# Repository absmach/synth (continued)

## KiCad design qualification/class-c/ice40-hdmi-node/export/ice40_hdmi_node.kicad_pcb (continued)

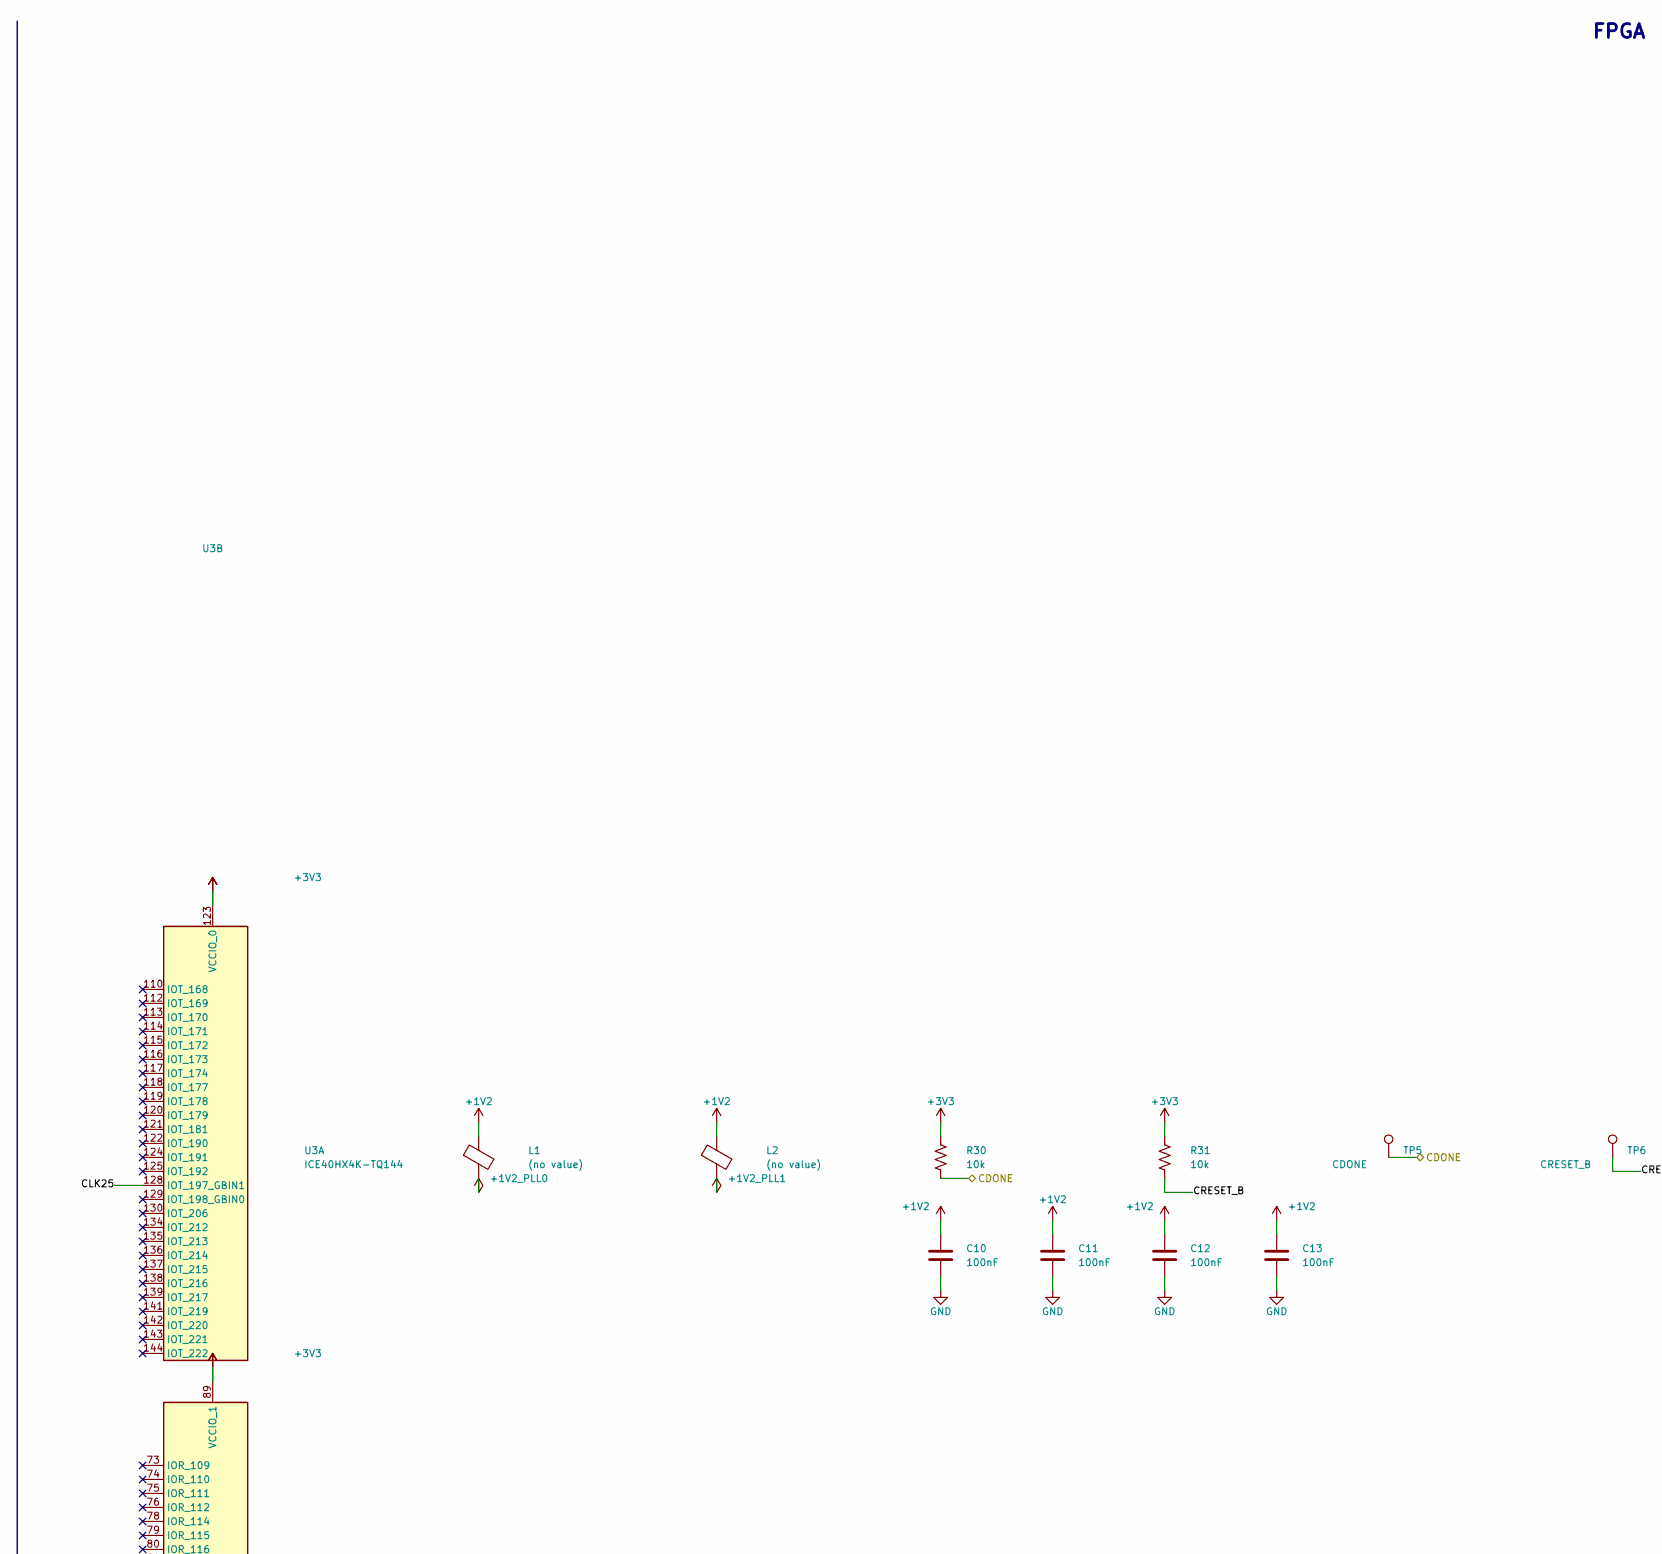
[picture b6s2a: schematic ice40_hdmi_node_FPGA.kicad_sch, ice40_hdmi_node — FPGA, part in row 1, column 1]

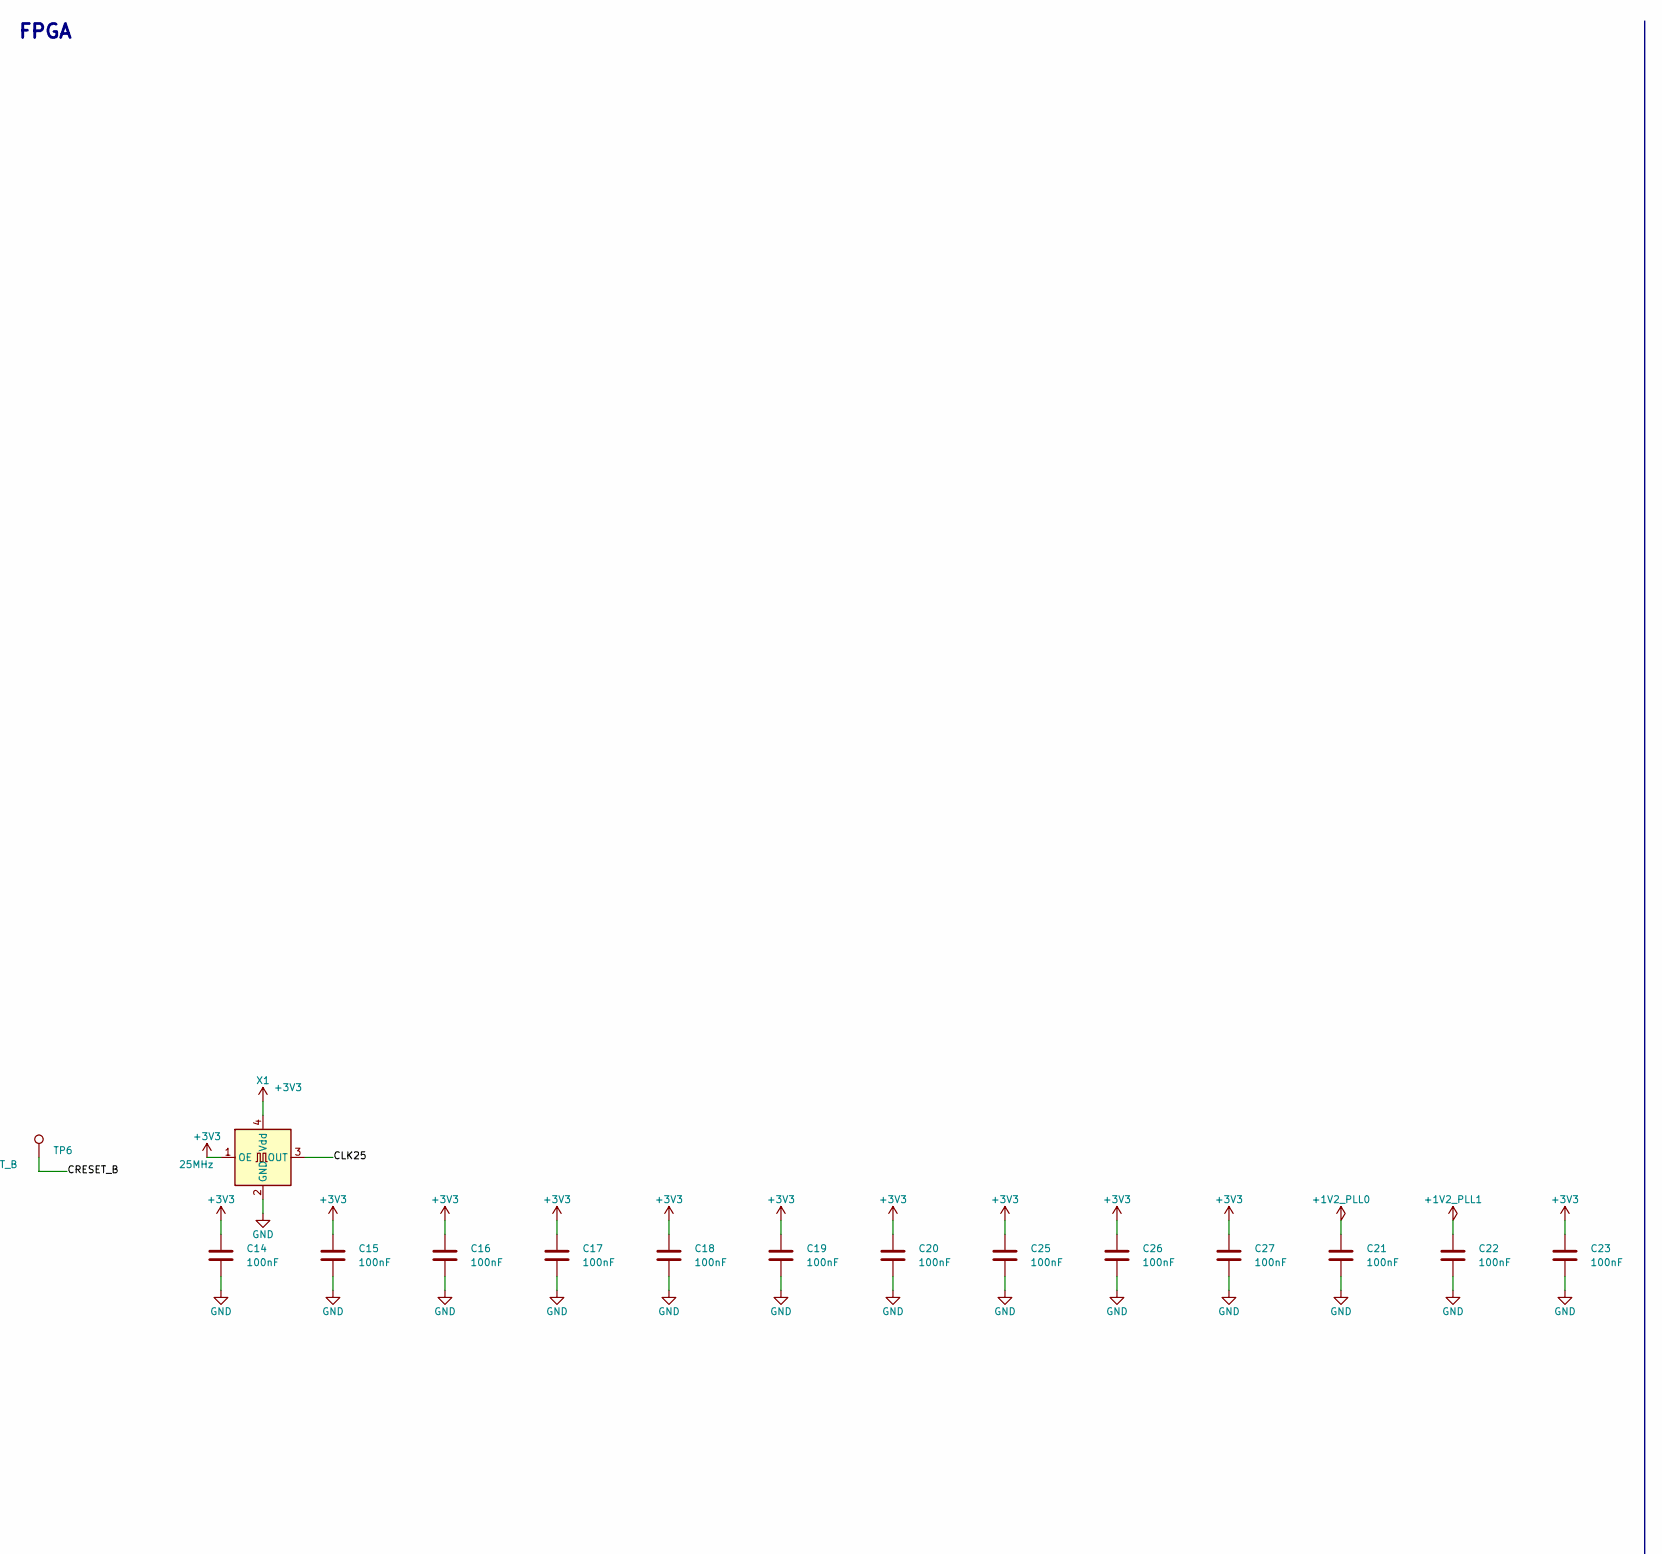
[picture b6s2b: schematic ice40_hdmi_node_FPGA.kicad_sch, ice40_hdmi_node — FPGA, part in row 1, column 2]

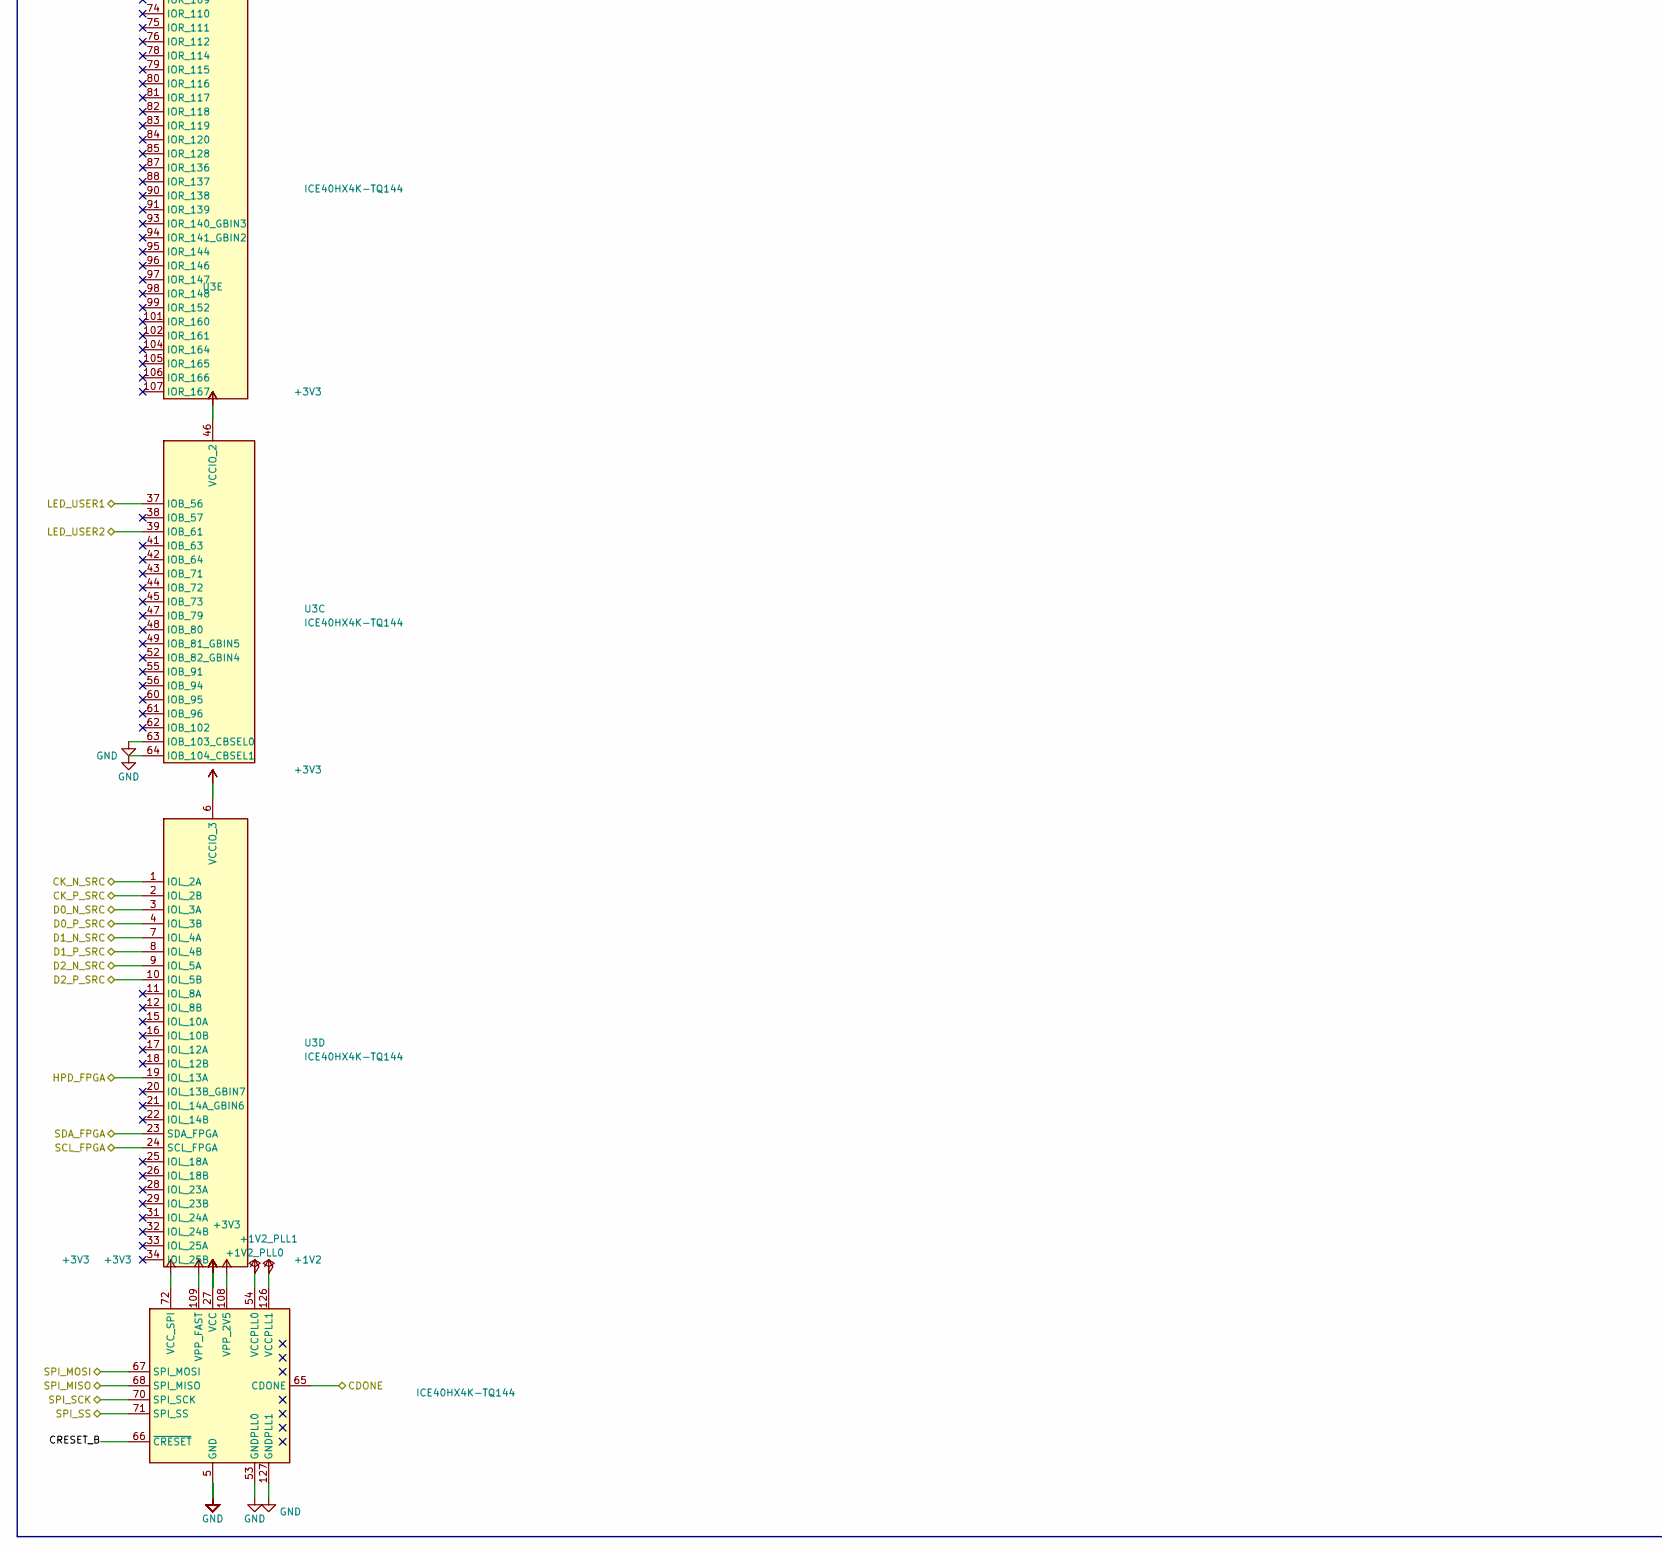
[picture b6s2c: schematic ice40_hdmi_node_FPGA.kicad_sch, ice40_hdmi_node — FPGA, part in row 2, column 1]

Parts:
C10, C11, C12, C13, C14, C15, C16, C17, C18, C19, C20, C21, C22, C23, C25, C26, C27: 100nF; C_0402_1005Metric
L1, L2: (no value); L_0603_1608Metric
R30, R31: 10k; R_0603_1608Metric
TP5: CDONE; TestPoint_Pad_D1.5mm
TP6: CRESET_B; TestPoint_Pad_D1.5mm
U3: ICE40HX4K-TQ144; TQFP-144_20x20mm_P0.5mm; MPN ICE40HX4K-TQ144
X1: 25MHz; Oscillator_SMD_SiT_PQFN-4Pin_5.0x3.2mm

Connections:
+1V2: C10.1, C11.1, C12.1, C13.1, L1.1, L2.1, U3.27 (VCC), U3.40 (VCC), U3.92 (VCC), U3.111 (VCC); also elsewhere on the board
+1V2_PLL0: C21.1, L1.2, U3.54 (VCCPLL0)
+1V2_PLL1: C22.1, L2.2, U3.126 (VCCPLL1)
+3V3: C14.1, C15.1, C16.1, C17.1, C18.1, C19.1, C20.1, C23.1, C25.1, C26.1, C27.1, R30.1, R31.1, U3.6 (VCCIO_3), U3.30 (VCCIO_3), U3.46 (VCCIO_2), U3.57 (VCCIO_2), U3.72 (VCC_SPI), U3.89 (VCCIO_1), U3.100 (VCCIO_1), U3.108 (VPP_2V5), U3.109 (VPP_FAST), U3.123 (VCCIO_0), U3.131 (VCCIO_0), X1.1 (OE), X1.4 (Vdd); also elsewhere on the board
CDONE: R30.2, TP5.1, U3.65 (CDONE); also elsewhere on the board
CK_N_SRC: U3.1 (IOL_2A); also elsewhere on the board
CK_P_SRC: U3.2 (IOL_2B); also elsewhere on the board
CLK25: U3.128 (IOT_197_GBIN1), X1.3 (OUT)
CRESET_B: R31.2, TP6.1, U3.66 (~CRESET)
D0_N_SRC: U3.3 (IOL_3A); also elsewhere on the board
D0_P_SRC: U3.4 (IOL_3B); also elsewhere on the board
D1_N_SRC: U3.7 (IOL_4A); also elsewhere on the board
D1_P_SRC: U3.8 (IOL_4B); also elsewhere on the board
D2_N_SRC: U3.9 (IOL_5A); also elsewhere on the board
D2_P_SRC: U3.10 (IOL_5B); also elsewhere on the board
GND: C10.2, C11.2, C12.2, C13.2, C14.2, C15.2, C16.2, C17.2, C18.2, C19.2, C20.2, C21.2, C22.2, C23.2, C25.2, C26.2, C27.2, U3.5 (GND), U3.13 (GND), U3.14 (GND), U3.53 (GNDPLL0), U3.59 (GND), U3.63 (IOB_103_CBSEL0), U3.64 (IOB_104_CBSEL1), U3.69 (GND), U3.86 (GND), U3.103 (GND), U3.127 (GNDPLL1), U3.132 (GND), U3.140 (GND), X1.2 (GND); also elsewhere on the board
HPD_FPGA: U3.19 (IOL_13A); also elsewhere on the board
LED_USER1: U3.37 (IOB_56); also elsewhere on the board
LED_USER2: U3.39 (IOB_61); also elsewhere on the board
SCL_FPGA: U3.24 (IOL_17B); also elsewhere on the board
SDA_FPGA: U3.23 (IOL_17A); also elsewhere on the board
SPI_MISO: U3.68 (IOB_106_SDI); also elsewhere on the board
SPI_MOSI: U3.67 (IOB_105_SDO); also elsewhere on the board
SPI_SCK: U3.70 (IOB_107_SCK); also elsewhere on the board
SPI_SS: U3.71 (IOB_108_SS); also elsewhere on the board

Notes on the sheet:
FPGA

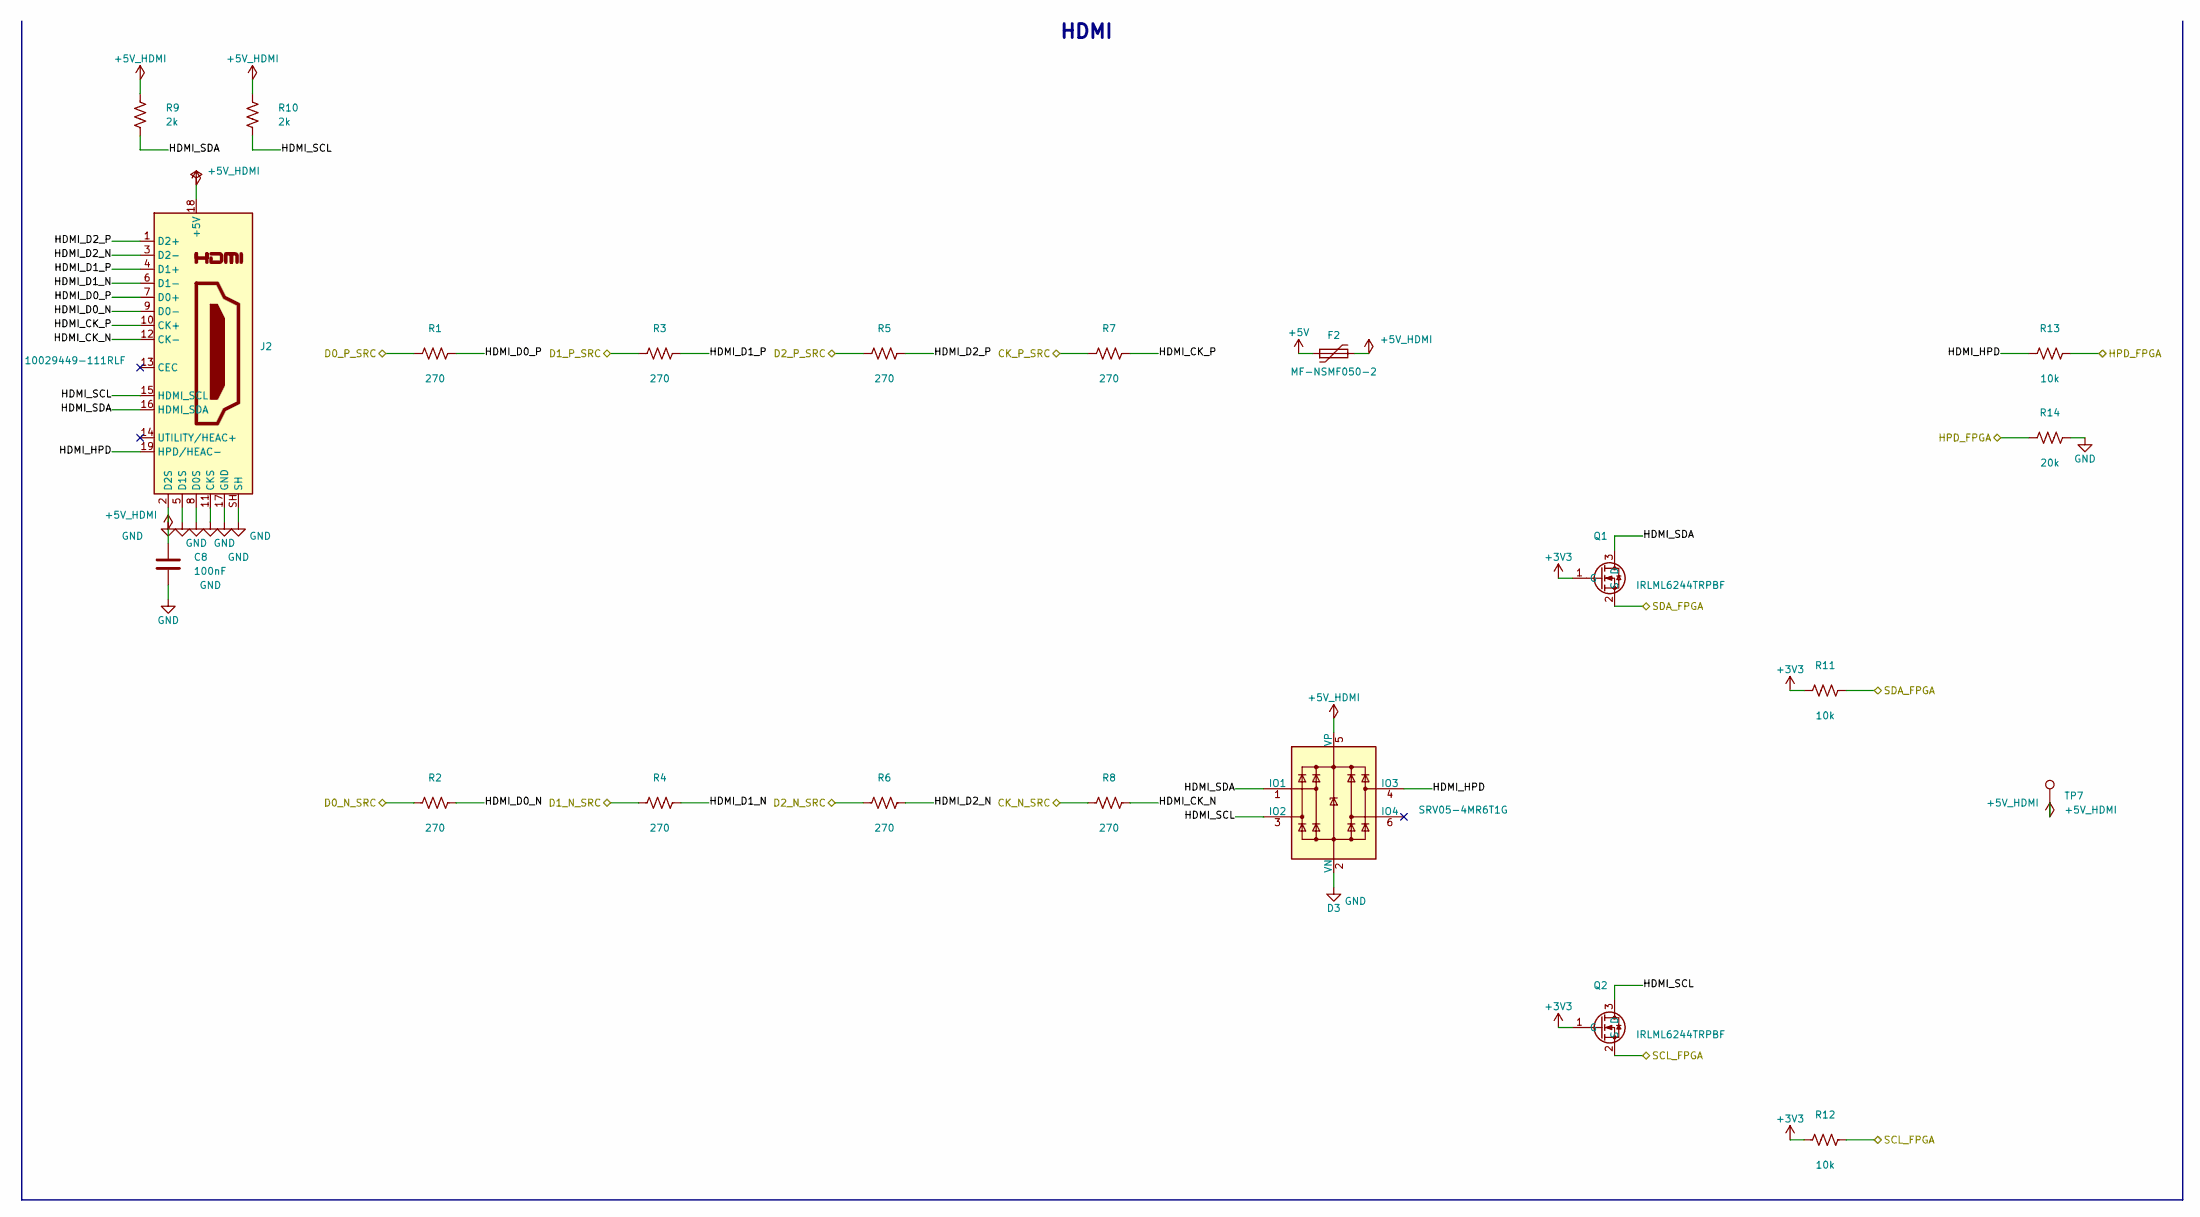
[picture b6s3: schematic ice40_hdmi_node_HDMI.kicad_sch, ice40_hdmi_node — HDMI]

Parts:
C8: 100nF; C_0603_1608Metric
D3: SRV05-4MR6T1G; SOT-23-6; MPN SRV05-4MR6T1G
F2: MF-NSMF050-2; Fuse_1206_3216Metric; MPN MF-NSMF050-2; LCSC C75464
J2: 10029449-111RLF; HDMI_A_Amphenol_10029449-x01xLF_Horizontal; MPN 10029449-111RLF
Q1, Q2: IRLML6244TRPBF; SOT-23; MPN IRLML6244TRPBF; LCSC C143946
R1, R2, R3, R4, R5, R6, R7, R8: 270; R_0603_1608Metric
R9, R10: 2k; R_0603_1608Metric
R11, R12, R13: 10k; R_0603_1608Metric
R14: 20k; R_0603_1608Metric
TP7: +5V_HDMI; TestPoint_Pad_D1.5mm

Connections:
+3V3: Q1.1 (G), Q2.1 (G), R11.1, R12.1; also elsewhere on the board
+5V: F2.1; also elsewhere on the board
+5V_HDMI: C8.1, D3.5 (VP), F2.2, J2.18 (+5V), R9.1, R10.1, TP7.1
CK_N_SRC: R8.1; also elsewhere on the board
CK_P_SRC: R7.1; also elsewhere on the board
D0_N_SRC: R2.1; also elsewhere on the board
D0_P_SRC: R1.1; also elsewhere on the board
D1_N_SRC: R4.1; also elsewhere on the board
D1_P_SRC: R3.1; also elsewhere on the board
D2_N_SRC: R6.1; also elsewhere on the board
D2_P_SRC: R5.1; also elsewhere on the board
GND: C8.2, D3.2 (VN), J2.2 (D2S), J2.5 (D1S), J2.8 (D0S), J2.11 (CKS), J2.17 (GND), J2.SH, R14.2; also elsewhere on the board
HDMI_CK_N: J2.12 (CK-), R8.2
HDMI_CK_P: J2.10 (CK+), R7.2
HDMI_D0_N: J2.9 (D0-), R2.2
HDMI_D0_P: J2.7 (D0+), R1.2
HDMI_D1_N: J2.6 (D1-), R4.2
HDMI_D1_P: J2.4 (D1+), R3.2
HDMI_D2_N: J2.3 (D2-), R6.2
HDMI_D2_P: J2.1 (D2+), R5.2
HDMI_HPD: D3.4 (IO3), J2.19 (HPD/HEAC-), R13.1
HDMI_SCL: D3.3 (IO2), J2.15 (SCL), Q2.3 (D), R10.2
HDMI_SDA: D3.1 (IO1), J2.16 (SDA), Q1.3 (D), R9.2
HPD_FPGA: R13.2, R14.1; also elsewhere on the board
SCL_FPGA: Q2.2 (S), R12.2; also elsewhere on the board
SDA_FPGA: Q1.2 (S), R11.2; also elsewhere on the board

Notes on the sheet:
HDMI

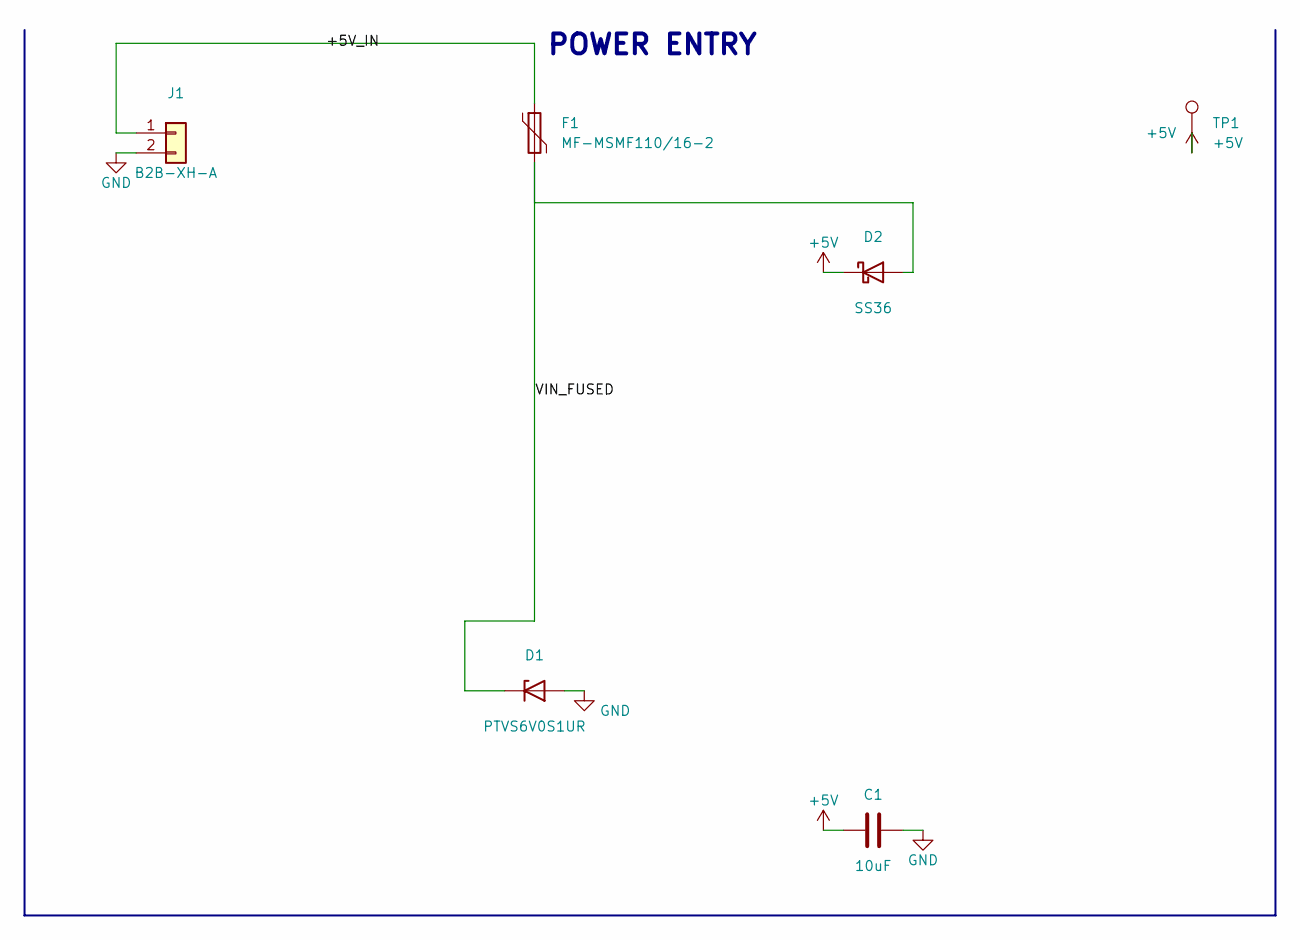
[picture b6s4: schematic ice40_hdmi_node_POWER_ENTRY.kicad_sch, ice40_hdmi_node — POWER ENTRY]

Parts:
C1: 10uF; C_0805_2012Metric
D1: PTVS6V0S1UR; Nexperia_CFP3_SOD-123W; MPN PTVS6V0S1UR
D2: SS36; D_SMC; MPN SS36
F1: MF-MSMF110/16-2; Fuse_1812_4532Metric; MPN MF-MSMF110/16-2; LCSC C210834
J1: B2B-XH-A; JST_XH_B2B-XH-A_1x02_P2.50mm_Vertical; MPN B2B-XH-A
TP1: +5V; TestPoint_Pad_D1.5mm

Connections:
+5V: C1.1, D2.1 (K), TP1.1; also elsewhere on the board
+5V_IN: F1.1, J1.1
GND: C1.2, D1.2 (A), J1.2; also elsewhere on the board
VIN_FUSED: D1.1 (K), D2.2 (A), F1.2

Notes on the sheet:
POWER ENTRY

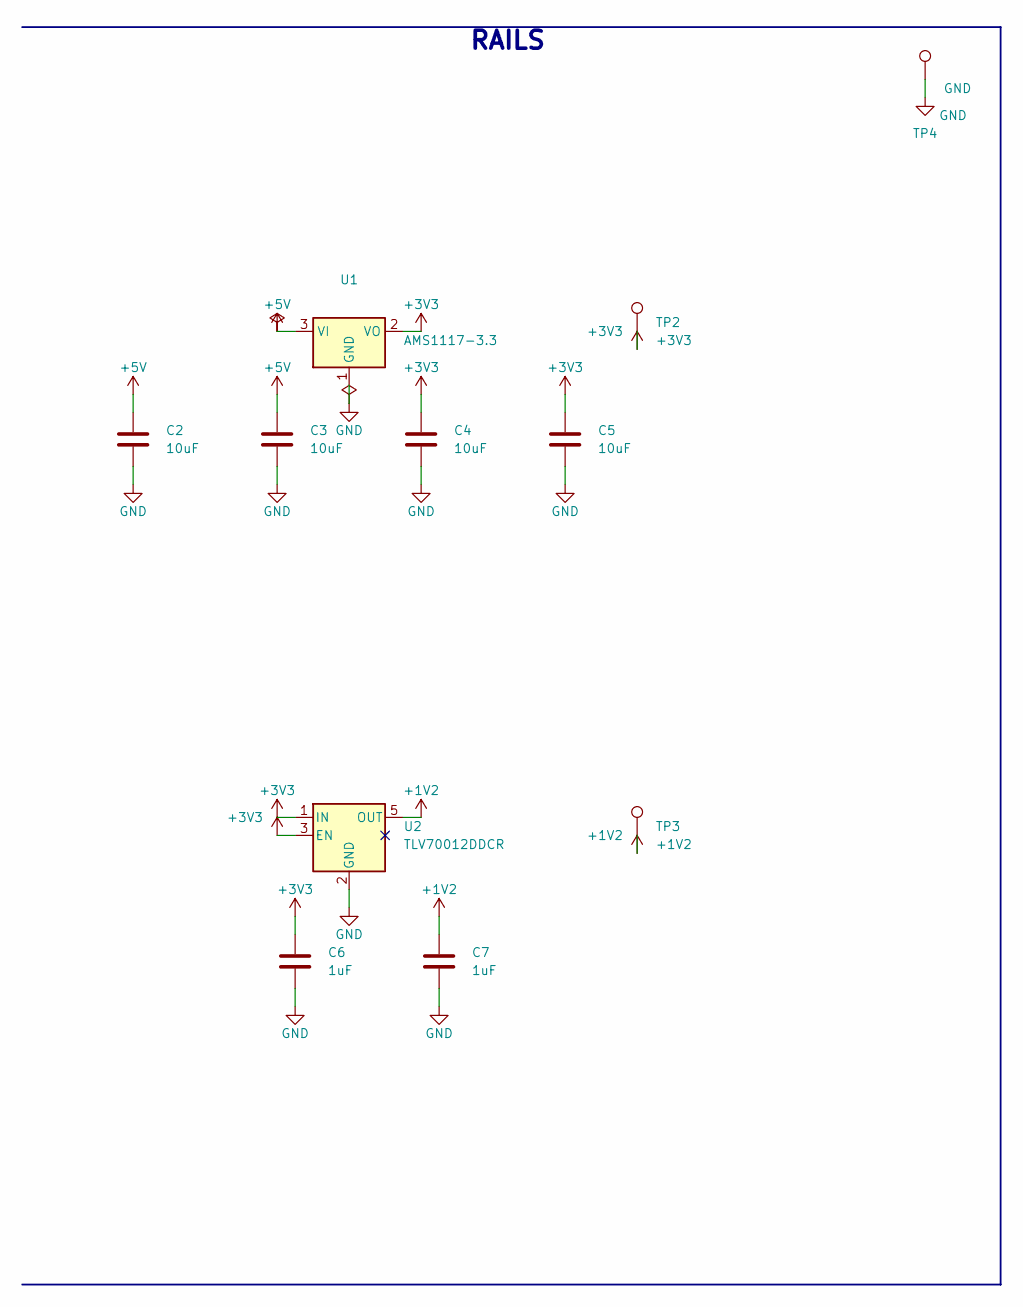
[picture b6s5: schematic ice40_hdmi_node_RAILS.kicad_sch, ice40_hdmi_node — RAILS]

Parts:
C2, C3, C4, C5: 10uF; C_0805_2012Metric
C6, C7: 1uF; C_0603_1608Metric
TP2: +3V3; TestPoint_Pad_D1.5mm
TP3: +1V2; TestPoint_Pad_D1.5mm
TP4: GND; TestPoint_Pad_D1.5mm
U1: AMS1117-3.3; SOT-223-3_TabPin2; MPN AMS1117-3.3; LCSC C6186
U2: TLV70012DDCR; TSOT-23-5; MPN TLV70012DDCR

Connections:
+1V2: C7.1, TP3.1, U2.5 (OUT); also elsewhere on the board
+3V3: C4.1, C5.1, C6.1, TP2.1, U1.2 (VO), U2.1 (IN), U2.3 (EN); also elsewhere on the board
+5V: C2.1, C3.1, U1.3 (VI); also elsewhere on the board
GND: C2.2, C3.2, C4.2, C5.2, C6.2, C7.2, TP4.1, U1.1 (GND), U2.2 (GND); also elsewhere on the board

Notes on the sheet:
RAILS

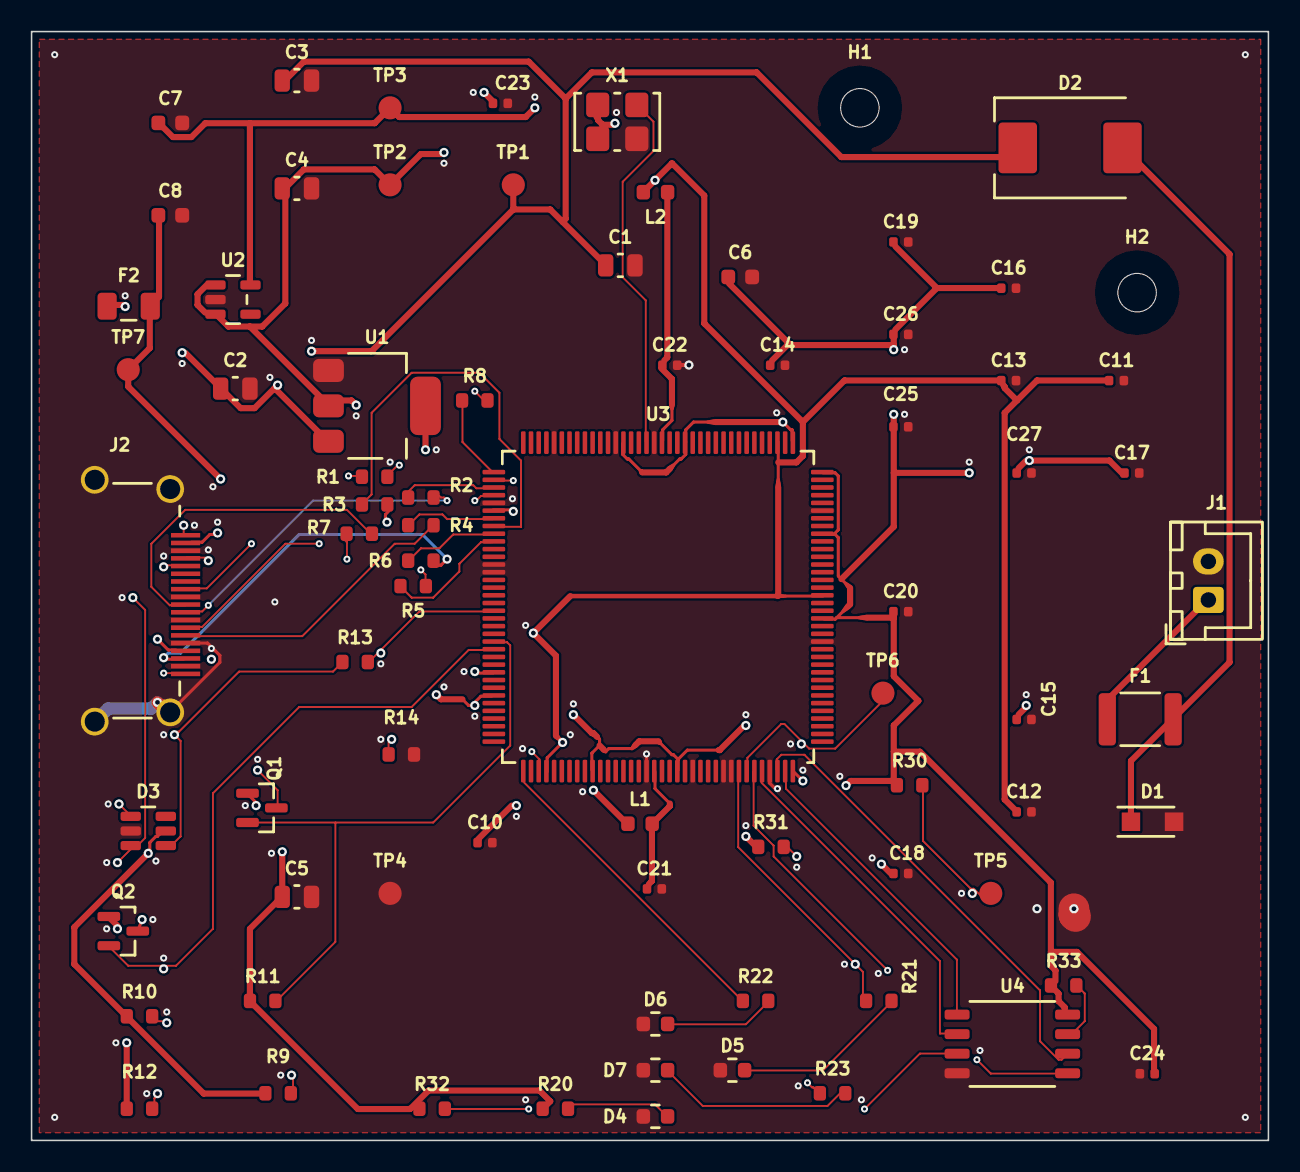
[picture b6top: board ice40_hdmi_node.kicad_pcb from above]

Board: 6 copper layers, 80.3 x 72.0 mm, 77 parts (0 on the bottom side), 46 nets.

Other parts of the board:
D4, D5: 0603-GREEN; LED_0603_1608Metric
D6, D7: 0603-RED; LED_0603_1608Metric
H1, H2: (no value); MountingHole_2.5mm
R20, R21, R22, R23: 470; R_0603_1608Metric

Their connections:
+3V3: R20.1; also elsewhere on the board
CDONE: R21.1; also elsewhere on the board
GND: D4.1, D5.1, D6.1, D7.1; also elsewhere on the board
LED1_A: D6.2, R22.2
LED2_A: D7.2, R23.2
LED_DONE: D5.2, R21.2
LED_PWR: D4.2, R20.2
LED_USER1: R22.1; also elsewhere on the board
LED_USER2: R23.1; also elsewhere on the board

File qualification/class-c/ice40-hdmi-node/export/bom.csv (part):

refdes,value,kind,description,kicad_symbol,kicad_footprint,lcsc_pn,mpn
C1,10uF,capacitor,"Generic 0805 MLCC, X7R/X5R, any value",Device:C,Capacitor_SMD:C_0805_2012Metric,,
C10,100nF,capacitor,"Generic 0402 MLCC, X7R/X5R, any value",Device:C,Capacitor_SMD:C_0402_1005Metric,,
C11,100nF,capacitor,"Generic 0402 MLCC, X7R/X5R, any value",Device:C,Capacitor_SMD:C_0402_1005Metric,,
C12,100nF,capacitor,"Generic 0402 MLCC, X7R/X5R, any value",Device:C,Capacitor_SMD:C_0402_1005Metric,,
C13,100nF,capacitor,"Generic 0402 MLCC, X7R/X5R, any value",Device:C,Capacitor_SMD:C_0402_1005Metric,,
C14,100nF,capacitor,"Generic 0402 MLCC, X7R/X5R, any value",Device:C,Capacitor_SMD:C_0402_1005Metric,,
C15,100nF,capacitor,"Generic 0402 MLCC, X7R/X5R, any value",Device:C,Capacitor_SMD:C_0402_1005Metric,,
C16,100nF,capacitor,"Generic 0402 MLCC, X7R/X5R, any value",Device:C,Capacitor_SMD:C_0402_1005Metric,,
C17,100nF,capacitor,"Generic 0402 MLCC, X7R/X5R, any value",Device:C,Capacitor_SMD:C_0402_1005Metric,,
C18,100nF,capacitor,"Generic 0402 MLCC, X7R/X5R, any value",Device:C,Capacitor_SMD:C_0402_1005Metric,,
C19,100nF,capacitor,"Generic 0402 MLCC, X7R/X5R, any value",Device:C,Capacitor_SMD:C_0402_1005Metric,,
C2,10uF,capacitor,"Generic 0805 MLCC, X7R/X5R, any value",Device:C,Capacitor_SMD:C_0805_2012Metric,,
C20,100nF,capacitor,"Generic 0402 MLCC, X7R/X5R, any value",Device:C,Capacitor_SMD:C_0402_1005Metric,,
C21,100nF,capacitor,"Generic 0402 MLCC, X7R/X5R, any value",Device:C,Capacitor_SMD:C_0402_1005Metric,,
C22,100nF,capacitor,"Generic 0402 MLCC, X7R/X5R, any value",Device:C,Capacitor_SMD:C_0402_1005Metric,,
C23,100nF,capacitor,"Generic 0402 MLCC, X7R/X5R, any value",Device:C,Capacitor_SMD:C_0402_1005Metric,,
C24,100nF,capacitor,"Generic 0402 MLCC, X7R/X5R, any value",Device:C,Capacitor_SMD:C_0402_1005Metric,,
C25,100nF,capacitor,"Generic 0402 MLCC, X7R/X5R, any value",Device:C,Capacitor_SMD:C_0402_1005Metric,,
C26,100nF,capacitor,"Generic 0402 MLCC, X7R/X5R, any value",Device:C,Capacitor_SMD:C_0402_1005Metric,,
C27,100nF,capacitor,"Generic 0402 MLCC, X7R/X5R, any value",Device:C,Capacitor_SMD:C_0402_1005Metric,,
C3,10uF,capacitor,"Generic 0805 MLCC, X7R/X5R, any value",Device:C,Capacitor_SMD:C_0805_2012Metric,,
C4,10uF,capacitor,"Generic 0805 MLCC, X7R/X5R, any value",Device:C,Capacitor_SMD:C_0805_2012Metric,,
C5,10uF,capacitor,"Generic 0805 MLCC, X7R/X5R, any value",Device:C,Capacitor_SMD:C_0805_2012Metric,,
C6,1uF,capacitor,"Generic 0603 MLCC, X7R/X5R, any value",Device:C,Capacitor_SMD:C_0603_1608Metric,,
C7,1uF,capacitor,"Generic 0603 MLCC, X7R/X5R, any value",Device:C,Capacitor_SMD:C_0603_1608Metric,,
C8,100nF,capacitor,"Generic 0603 MLCC, X7R/X5R, any value",Device:C,Capacitor_SMD:C_0603_1608Metric,,
D1,PTVS6V0S1UR,diode,"Nexperia PTVS6V0S1UR 400 W unidirectional TVS, 6.0 V standoff, SOD123W, for VBUS and CC",Device:D_Zener,Diode_SMD:Nexperia_CFP3_SOD-123W,,PTVS6V0S1UR
D2,SS36,diode,"Vishay SS36 60 V 3 A Schottky rectifier, SMC (DO-214AB), for reverse-polarity blocking",Device:D_Schottky,Diode_SMD:D_SMC,,SS36
D3,SRV05-4MR6T1G,diode,"onsemi SRV05-4 4-line surge/ESD protection array, 5 V working voltage, TSOP-6 (SOT-23-6 footprint compatible)",Power_Protection:SRV05-4,Package_TO_SOT_SMD:SOT-23-6,,SRV05-4MR6T1G
D4,0603-GREEN,led,"Green LED, 0603 package, ~2.2V Vf",Device:LED,LED_SMD:LED_0603_1608Metric,C72043,0603-GREEN
D5,0603-GREEN,led,"Green LED, 0603 package, ~2.2V Vf",Device:LED,LED_SMD:LED_0603_1608Metric,C72043,0603-GREEN
D6,0603-RED,led,"Red LED, 0603 package, ~2.0V Vf",Device:LED,LED_SMD:LED_0603_1608Metric,C2286,0603-RED
D7,0603-RED,led,"Red LED, 0603 package, ~2.0V Vf",Device:LED,LED_SMD:LED_0603_1608Metric,C2286,0603-RED
F1,MF-MSMF110/16-2,fuse,"Bourns MF-MSMF110/16-2 resettable fuse, 1.1 A hold, 16 V, 1812",Device:Polyfuse,Fuse:Fuse_1812_4532Metric,C210834,MF-MSMF110/16-2
F2,MF-NSMF050-2,fuse,"Bourns MF-NSMF050-2 resettable fuse, 0.5 A hold, 13.2 V, 1206",Device:Polyfuse,Fuse:Fuse_1206_3216Metric,C75464,MF-NSMF050-2
H1,(no value),mounting_hole,M2.5 non-plated mounting hole (NPTH) for a board corner,Mechanical:MountingHole,MountingHole:MountingHole_2.5mm,,
H2,(no value),mounting_hole,M2.5 non-plated mounting hole (NPTH) for a board corner,Mechanical:MountingHole,MountingHole:MountingHole_2.5mm,,
J1,B2B-XH-A,connector,"JST XH 2.5 mm pitch 2-pin vertical header B2B-XH-A, 250 V / 3 A per JST XH sheet",Connector_Generic:Conn_01x02,Connector_JST:JST_XH_B2B-XH-A_1x02_P2.50mm_Vertical,,B2B-XH-A
J2,10029449-111RLF,connector,"HDMI Type-A receptacle, 19-pin + shield, horizontal",Connector:HDMI_A_1.4,Connector_Video:HDMI_A_Amphenol_10029449-x01xLF_Horizontal,,10029449-111RLF
L1,(no value),inductor,"0603 ferrite bead, 600Ω @ 100MHz — EMI suppression",Device:FerriteBead,Inductor_SMD:L_0603_1608Metric,,
L2,(no value),inductor,"0603 ferrite bead, 600Ω @ 100MHz — EMI suppression",Device:FerriteBead,Inductor_SMD:L_0603_1608Metric,,
Q1,IRLML6244TRPBF,transistor,"IR IRLML6244 logic-level N-channel MOSFET, SOT-23",Transistor_FET:IRLML6244,Package_TO_SOT_SMD:SOT-23,C143946,IRLML6244TRPBF
Q2,IRLML6244TRPBF,transistor,"IR IRLML6244 logic-level N-channel MOSFET, SOT-23",Transistor_FET:IRLML6244,Package_TO_SOT_SMD:SOT-23,C143946,IRLML6244TRPBF
R1,270,resistor,"Generic 0603 thick-film resistor, any value",Device:R_US,Resistor_SMD:R_0603_1608Metric,,
R10,2k,resistor,"Generic 0603 thick-film resistor, any value",Device:R_US,Resistor_SMD:R_0603_1608Metric,,
R11,10k,resistor,"Generic 0603 thick-film resistor, any value",Device:R_US,Resistor_SMD:R_0603_1608Metric,,
R12,10k,resistor,"Generic 0603 thick-film resistor, any value",Device:R_US,Resistor_SMD:R_0603_1608Metric,,
R13,10k,resistor,"Generic 0603 thick-film resistor, any value",Device:R_US,Resistor_SMD:R_0603_1608Metric,,
R14,20k,resistor,"Generic 0603 thick-film resistor, any value",Device:R_US,Resistor_SMD:R_0603_1608Metric,,
R2,270,resistor,"Generic 0603 thick-film resistor, any value",Device:R_US,Resistor_SMD:R_0603_1608Metric,,
R20,470,resistor,"Generic 0603 thick-film resistor, any value",Device:R_US,Resistor_SMD:R_0603_1608Metric,,
R21,470,resistor,"Generic 0603 thick-film resistor, any value",Device:R_US,Resistor_SMD:R_0603_1608Metric,,
R22,470,resistor,"Generic 0603 thick-film resistor, any value",Device:R_US,Resistor_SMD:R_0603_1608Metric,,
R23,470,resistor,"Generic 0603 thick-film resistor, any value",Device:R_US,Resistor_SMD:R_0603_1608Metric,,
R3,270,resistor,"Generic 0603 thick-film resistor, any value",Device:R_US,Resistor_SMD:R_0603_1608Metric,,
R30,10k,resistor,"Generic 0603 thick-film resistor, any value",Device:R_US,Resistor_SMD:R_0603_1608Metric,,
R31,10k,resistor,"Generic 0603 thick-film resistor, any value",Device:R_US,Resistor_SMD:R_0603_1608Metric,,
R32,10k,resistor,"Generic 0603 thick-film resistor, any value",Device:R_US,Resistor_SMD:R_0603_1608Metric,,
R33,10k,resistor,"Generic 0603 thick-film resistor, any value",Device:R_US,Resistor_SMD:R_0603_1608Metric,,
R4,270,resistor,"Generic 0603 thick-film resistor, any value",Device:R_US,Resistor_SMD:R_0603_1608Metric,,
R5,270,resistor,"Generic 0603 thick-film resistor, any value",Device:R_US,Resistor_SMD:R_0603_1608Metric,,
R6,270,resistor,"Generic 0603 thick-film resistor, any value",Device:R_US,Resistor_SMD:R_0603_1608Metric,,
R7,270,resistor,"Generic 0603 thick-film resistor, any value",Device:R_US,Resistor_SMD:R_0603_1608Metric,,
R8,270,resistor,"Generic 0603 thick-film resistor, any value",Device:R_US,Resistor_SMD:R_0603_1608Metric,,
R9,2k,resistor,"Generic 0603 thick-film resistor, any value",Device:R_US,Resistor_SMD:R_0603_1608Metric,,
TP1,+5V,testpoint,"SMD test point pad, 1.5 mm — probe point for a net",Connector:TestPoint,TestPoint:TestPoint_Pad_D1.5mm,,
TP2,+3V3,testpoint,"SMD test point pad, 1.5 mm — probe point for a net",Connector:TestPoint,TestPoint:TestPoint_Pad_D1.5mm,,
TP3,+1V2,testpoint,"SMD test point pad, 1.5 mm — probe point for a net",Connector:TestPoint,TestPoint:TestPoint_Pad_D1.5mm,,
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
